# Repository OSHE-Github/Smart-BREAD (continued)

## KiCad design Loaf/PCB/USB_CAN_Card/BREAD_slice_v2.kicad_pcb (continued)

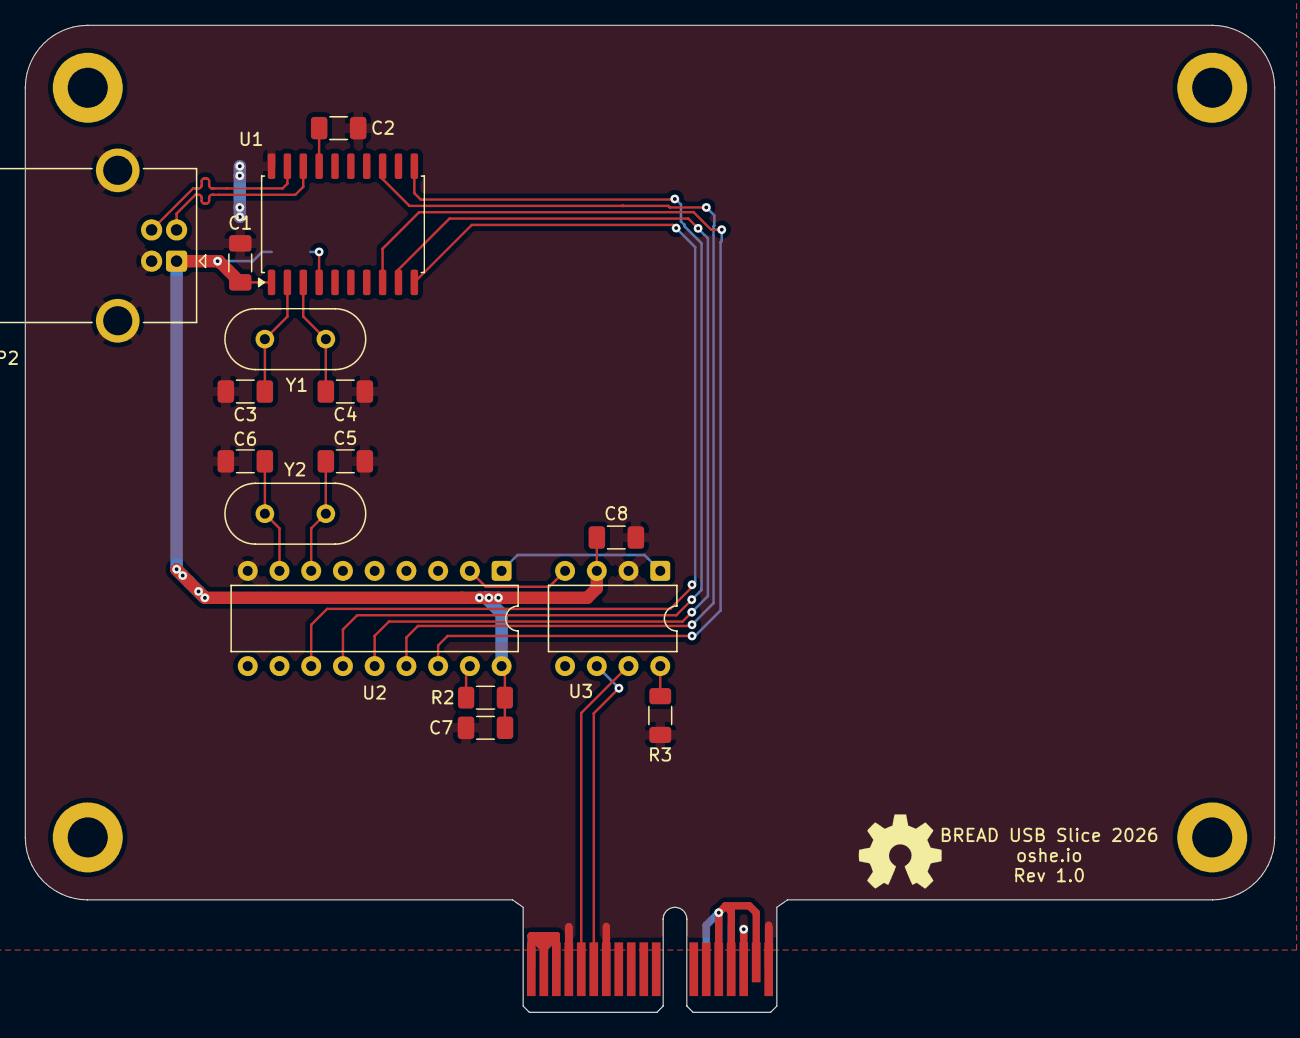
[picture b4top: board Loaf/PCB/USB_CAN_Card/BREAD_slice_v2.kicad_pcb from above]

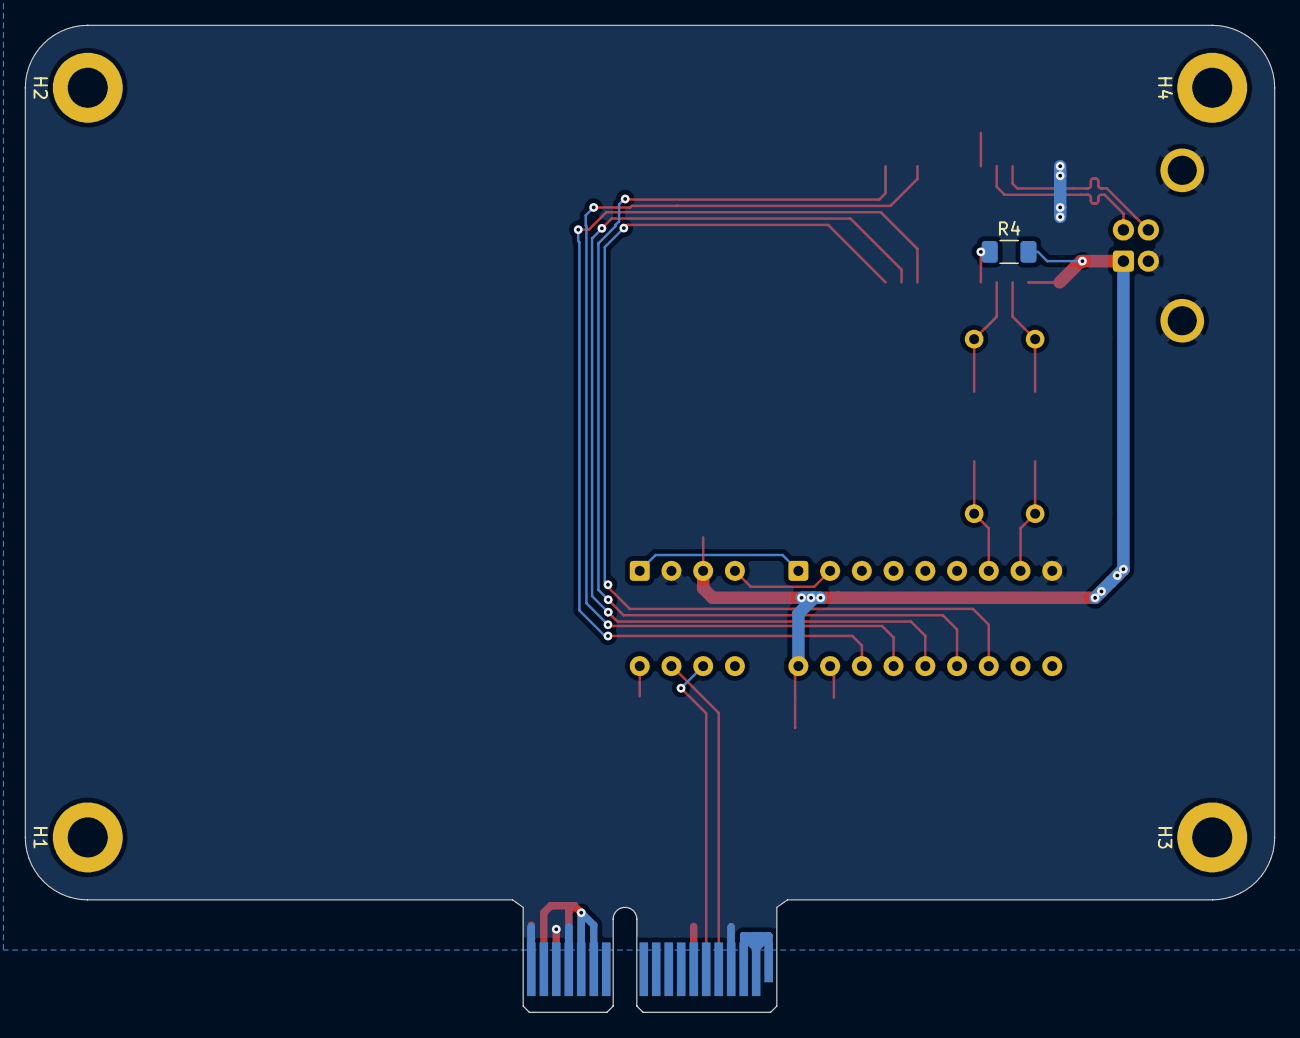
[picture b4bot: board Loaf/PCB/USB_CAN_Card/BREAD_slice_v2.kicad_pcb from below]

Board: 2 copper layers, 100.0 x 79.0 mm, 23 parts (5 on the bottom side), 24 nets.

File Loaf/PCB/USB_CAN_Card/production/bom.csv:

Designator,Footprint,Quantity,Value,LCSC Part #
C1,1206,1,1uF,
C2,1206,1,0.22-0.47uF,
"C3, C4, C5, C6",1206,4,20pf,
"C7, C8",1206,2,0.1uF,
J1,BUS_PCIexpress_x1,1,10018783-10200TLF,
LOGO1,OSHW-Symbol_6.7x6mm_SilkScreen,1,Logo_Open_Hardware_Small,
P2,USB_B_OST_USB-B1HSxx_Horizontal,1,USB_B,
"R2, R3, R4",1206,3,10k,
U1,SOIC-20W_7.5x12.8mm_P1.27mm,1,MCP2210x-SO,
U2,DIP-18_W7.62mm,1,MCP2515-xSO,
U3,DIP-8_W7.62mm,1,MCP2561-E-P,
Y1,Crystal_HC49-4H_Vertical,1,12MHZ Crystal,
Y2,Crystal_HC49-4H_Vertical,1,16MHZ Crystal,

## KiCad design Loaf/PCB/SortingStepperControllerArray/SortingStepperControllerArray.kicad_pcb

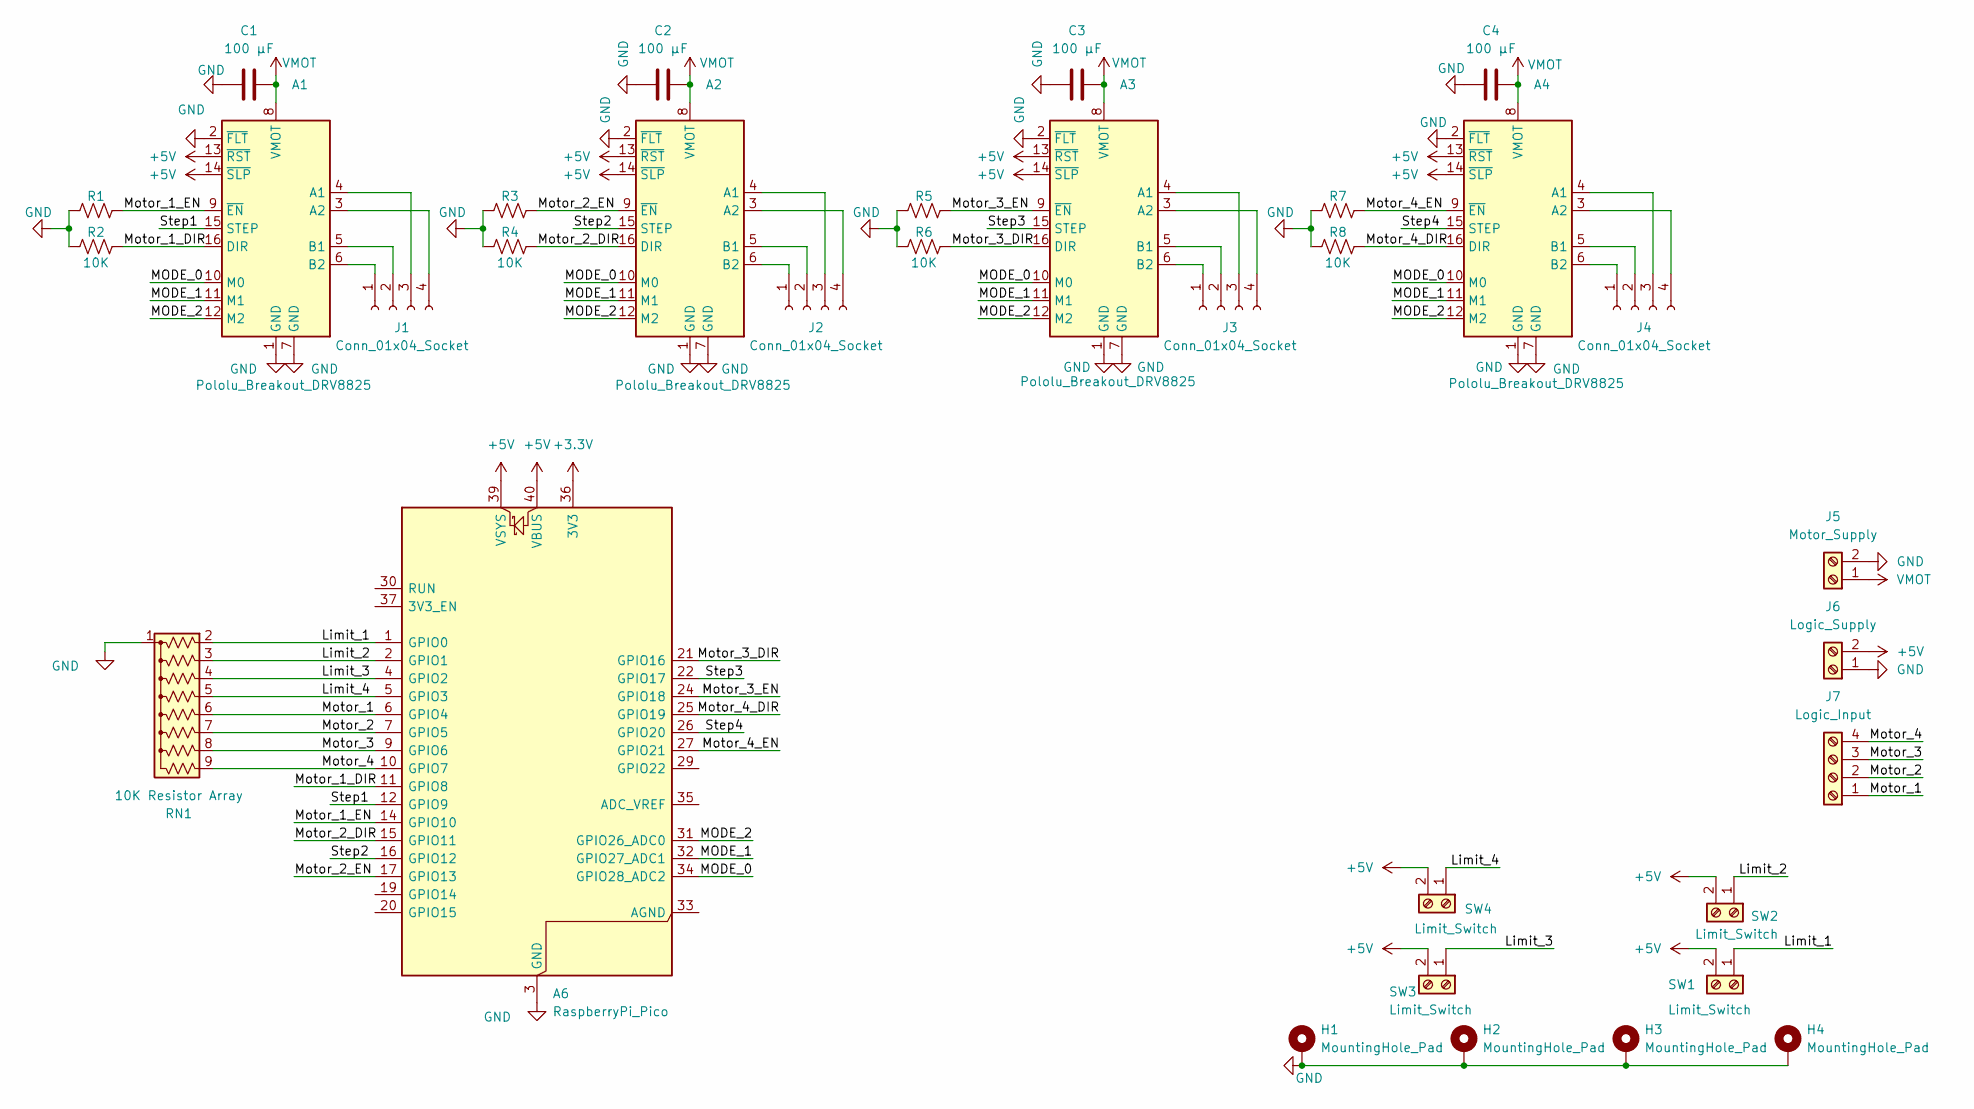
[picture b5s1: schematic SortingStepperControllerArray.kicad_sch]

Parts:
A1, A2, A3, A4: Pololu_Breakout_DRV8825; Pololu_Breakout-16_15.2x20.3mm
A6: RaspberryPi_Pico; RaspberryPi_Pico_Common_Unspecified
C1, C2, C3, C4: 100 µF; CP_Radial_D8.0mm_P3.50mm
H1, H2, H3, H4: MountingHole_Pad; MountingHole_3.2mm_M3_DIN965_Pad
J1, J2, J3, J4: Conn_01x04_Socket; JST_XH_B4B-XH-A_1x04_P2.50mm_Vertical
J5: Motor_Supply; TerminalBlock_TE_282834-2_1x02_P2.54mm_Horizontal
J6: Logic_Supply; TerminalBlock_TE_282834-2_1x02_P2.54mm_Horizontal
J7: Logic_Input; TerminalBlock_TE_282834-4_1x04_P2.54mm_Horizontal
R1, R2, R3, R4, R5, R6, R7, R8: 10K; R_1206_3216Metric_Pad1.30x1.75mm_HandSolder
RN1: 10K Resistor Array; R_Array_SIP9
SW1, SW2, SW3, SW4: Limit_Switch; TerminalBlock_TE_282834-2_1x02_P2.54mm_Horizontal

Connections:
+3.3V: A6.36 (3V3)
+5V: A1.13 (~RST), A1.14 (~SLP), A2.13 (~RST), A2.14 (~SLP), A3.13 (~RST), A3.14 (~SLP), A4.13 (~RST), A4.14 (~SLP), A6.39 (VSYS), A6.40 (VBUS), J6.2, SW1.2, SW2.2, SW3.2, SW4.2
/Limit_1: A6.1 (GPIO0), RN1.2 (R1), SW1.1
/Limit_2: A6.2 (GPIO1), RN1.3 (R2), SW2.1
/Limit_3: A6.4 (GPIO2), RN1.4 (R3), SW3.1
/Limit_4: A6.5 (GPIO3), RN1.5 (R4), SW4.1
/MODE_0: A1.10 (M0), A2.10 (M0), A3.10 (M0), A4.10 (M0), A6.34 (GPIO28_ADC2)
/MODE_1: A1.11 (M1), A2.11 (M1), A3.11 (M1), A4.11 (M1), A6.32 (GPIO27_ADC1)
/MODE_2: A1.12 (M2), A2.12 (M2), A3.12 (M2), A4.12 (M2), A6.31 (GPIO26_ADC0)
/Motor_1: A6.6 (GPIO4), J7.1, RN1.6 (R5)
/Motor_1_DIR: A1.16 (DIR), A6.11 (GPIO8), R2.2
/Motor_1_EN: A1.9 (~EN), A6.14 (GPIO10), R1.2
/Motor_2: A6.7 (GPIO5), J7.2, RN1.7 (R6)
/Motor_2_DIR: A2.16 (DIR), A6.15 (GPIO11), R4.2
/Motor_2_EN: A2.9 (~EN), A6.17 (GPIO13), R3.2
/Motor_3: A6.9 (GPIO6), J7.3, RN1.8 (R7)
/Motor_3_DIR: A3.16 (DIR), A6.21 (GPIO16), R6.2
/Motor_3_EN: A3.9 (~EN), A6.24 (GPIO18), R5.2
/Motor_4: A6.10 (GPIO7), J7.4, RN1.9 (R8)
/Motor_4_DIR: A4.16 (DIR), A6.25 (GPIO19), R8.2
/Motor_4_EN: A4.9 (~EN), A6.27 (GPIO21), R7.2
/Step1: A1.15 (STEP), A6.12 (GPIO9)
/Step2: A2.15 (STEP), A6.16 (GPIO12)
/Step3: A3.15 (STEP), A6.22 (GPIO17)
/Step4: A4.15 (STEP), A6.26 (GPIO20)
GND: A1.1 (GND), A1.2 (~FLT), A1.7 (GND), A2.1 (GND), A2.2 (~FLT), A2.7 (GND), A3.1 (GND), A3.2 (~FLT), A3.7 (GND), A4.1 (GND), A4.2 (~FLT), A4.7 (GND), A6.3 (GND), A6.8 (GND), A6.13 (GND), A6.18 (GND), A6.23 (GND), A6.28 (GND), A6.38 (GND), C1.1, C2.1, C3.1, C4.1, H1.1 (1_1), H2.1 (1_1), H3.1 (1_1), H4.1 (1_1), J5.2, J6.1, R1.1, R2.1, R3.1, R4.1, R5.1, R6.1, R7.1, R8.1, RN1.1 (common)
unnamed: A1.4 (A1), J1.3
unnamed: A1.3 (A2), J1.4
unnamed: A1.5 (B1), J1.2
unnamed: A1.6 (B2), J1.1
unnamed: A2.4 (A1), J2.3
unnamed: A2.3 (A2), J2.4
unnamed: A2.5 (B1), J2.2
unnamed: A2.6 (B2), J2.1
unnamed: A3.4 (A1), J3.3
unnamed: A3.3 (A2), J3.4
unnamed: A3.5 (B1), J3.2
unnamed: A3.6 (B2), J3.1
unnamed: A4.4 (A1), J4.3
unnamed: A4.3 (A2), J4.4
unnamed: A4.5 (B1), J4.2
unnamed: A4.6 (B2), J4.1
VMOT: A1.8 (VMOT), A2.8 (VMOT), A3.8 (VMOT), A4.8 (VMOT), C1.2, C2.2, C3.2, C4.2, J5.1

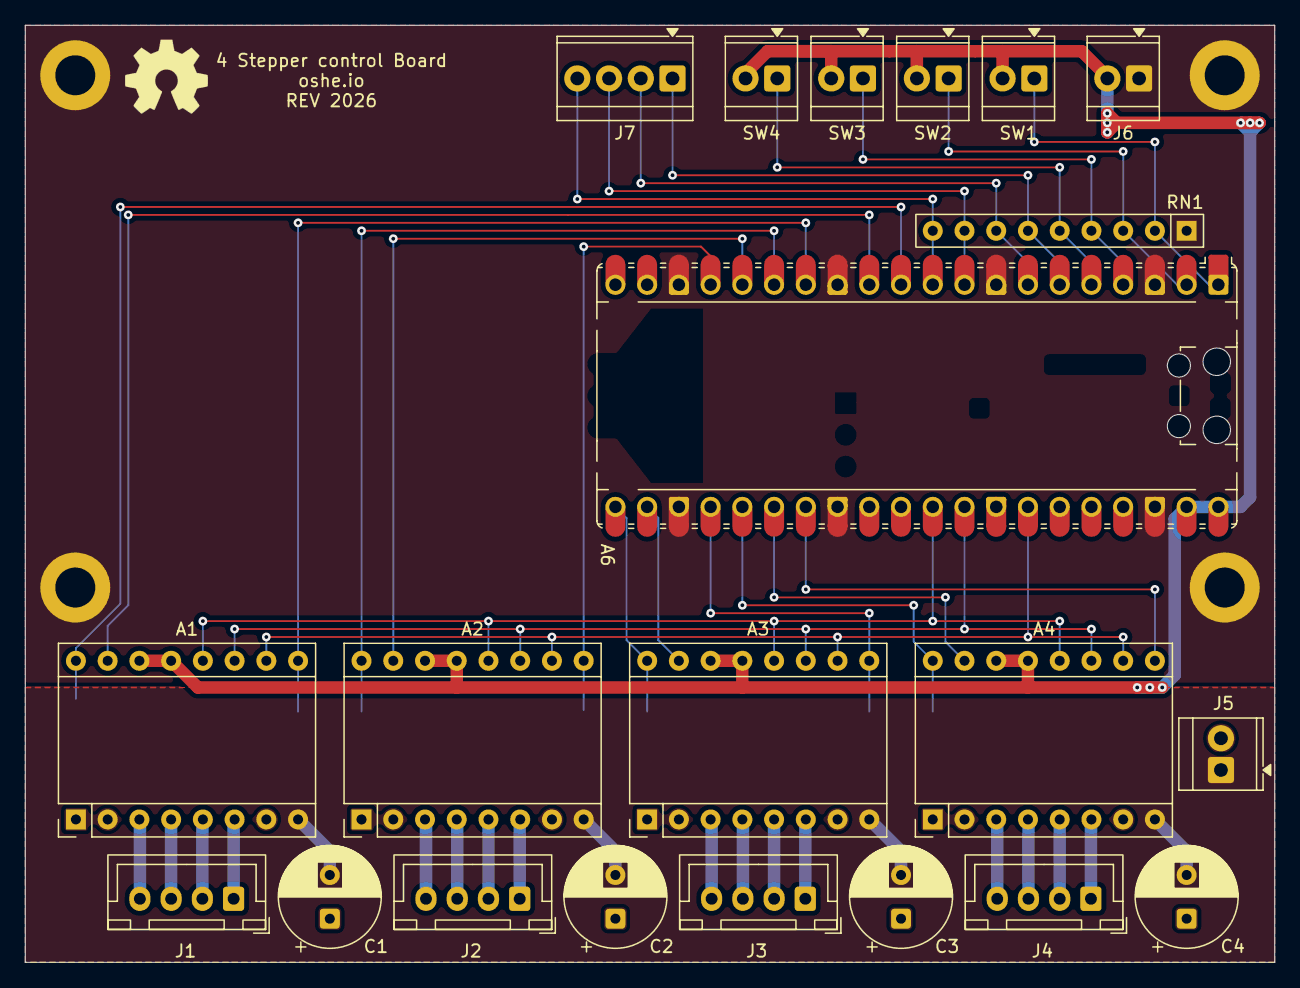
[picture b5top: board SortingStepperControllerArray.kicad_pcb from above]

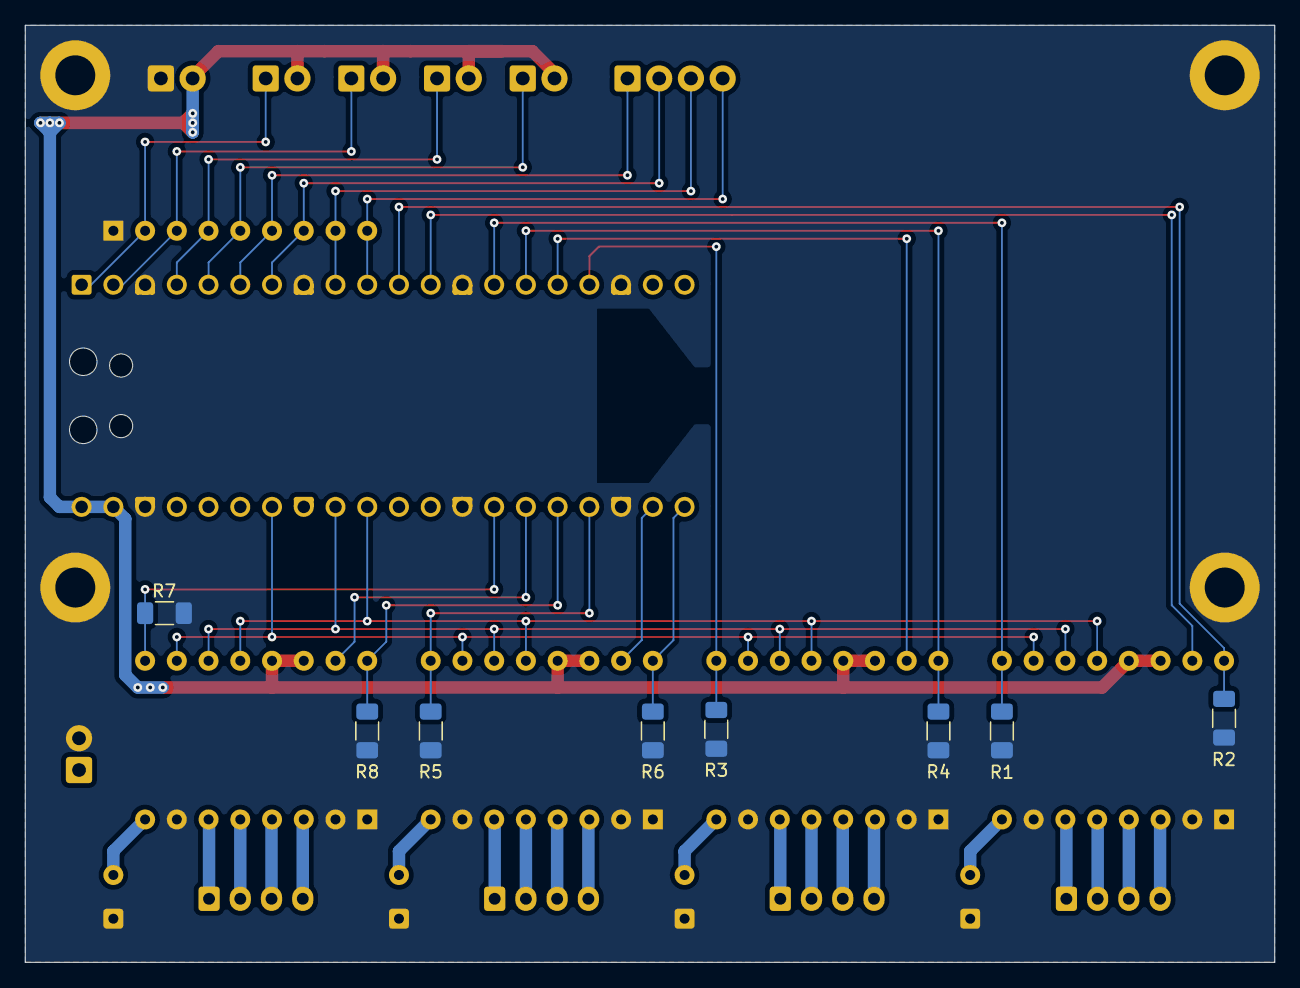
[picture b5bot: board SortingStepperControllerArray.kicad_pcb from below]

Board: 2 copper layers, 100.0 x 75.0 mm, 34 parts (8 on the bottom side), 42 nets.

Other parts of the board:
Logo1: Logo_Open_Hardware_Small; OSHW-Symbol_6.7x6mm_SilkScreen

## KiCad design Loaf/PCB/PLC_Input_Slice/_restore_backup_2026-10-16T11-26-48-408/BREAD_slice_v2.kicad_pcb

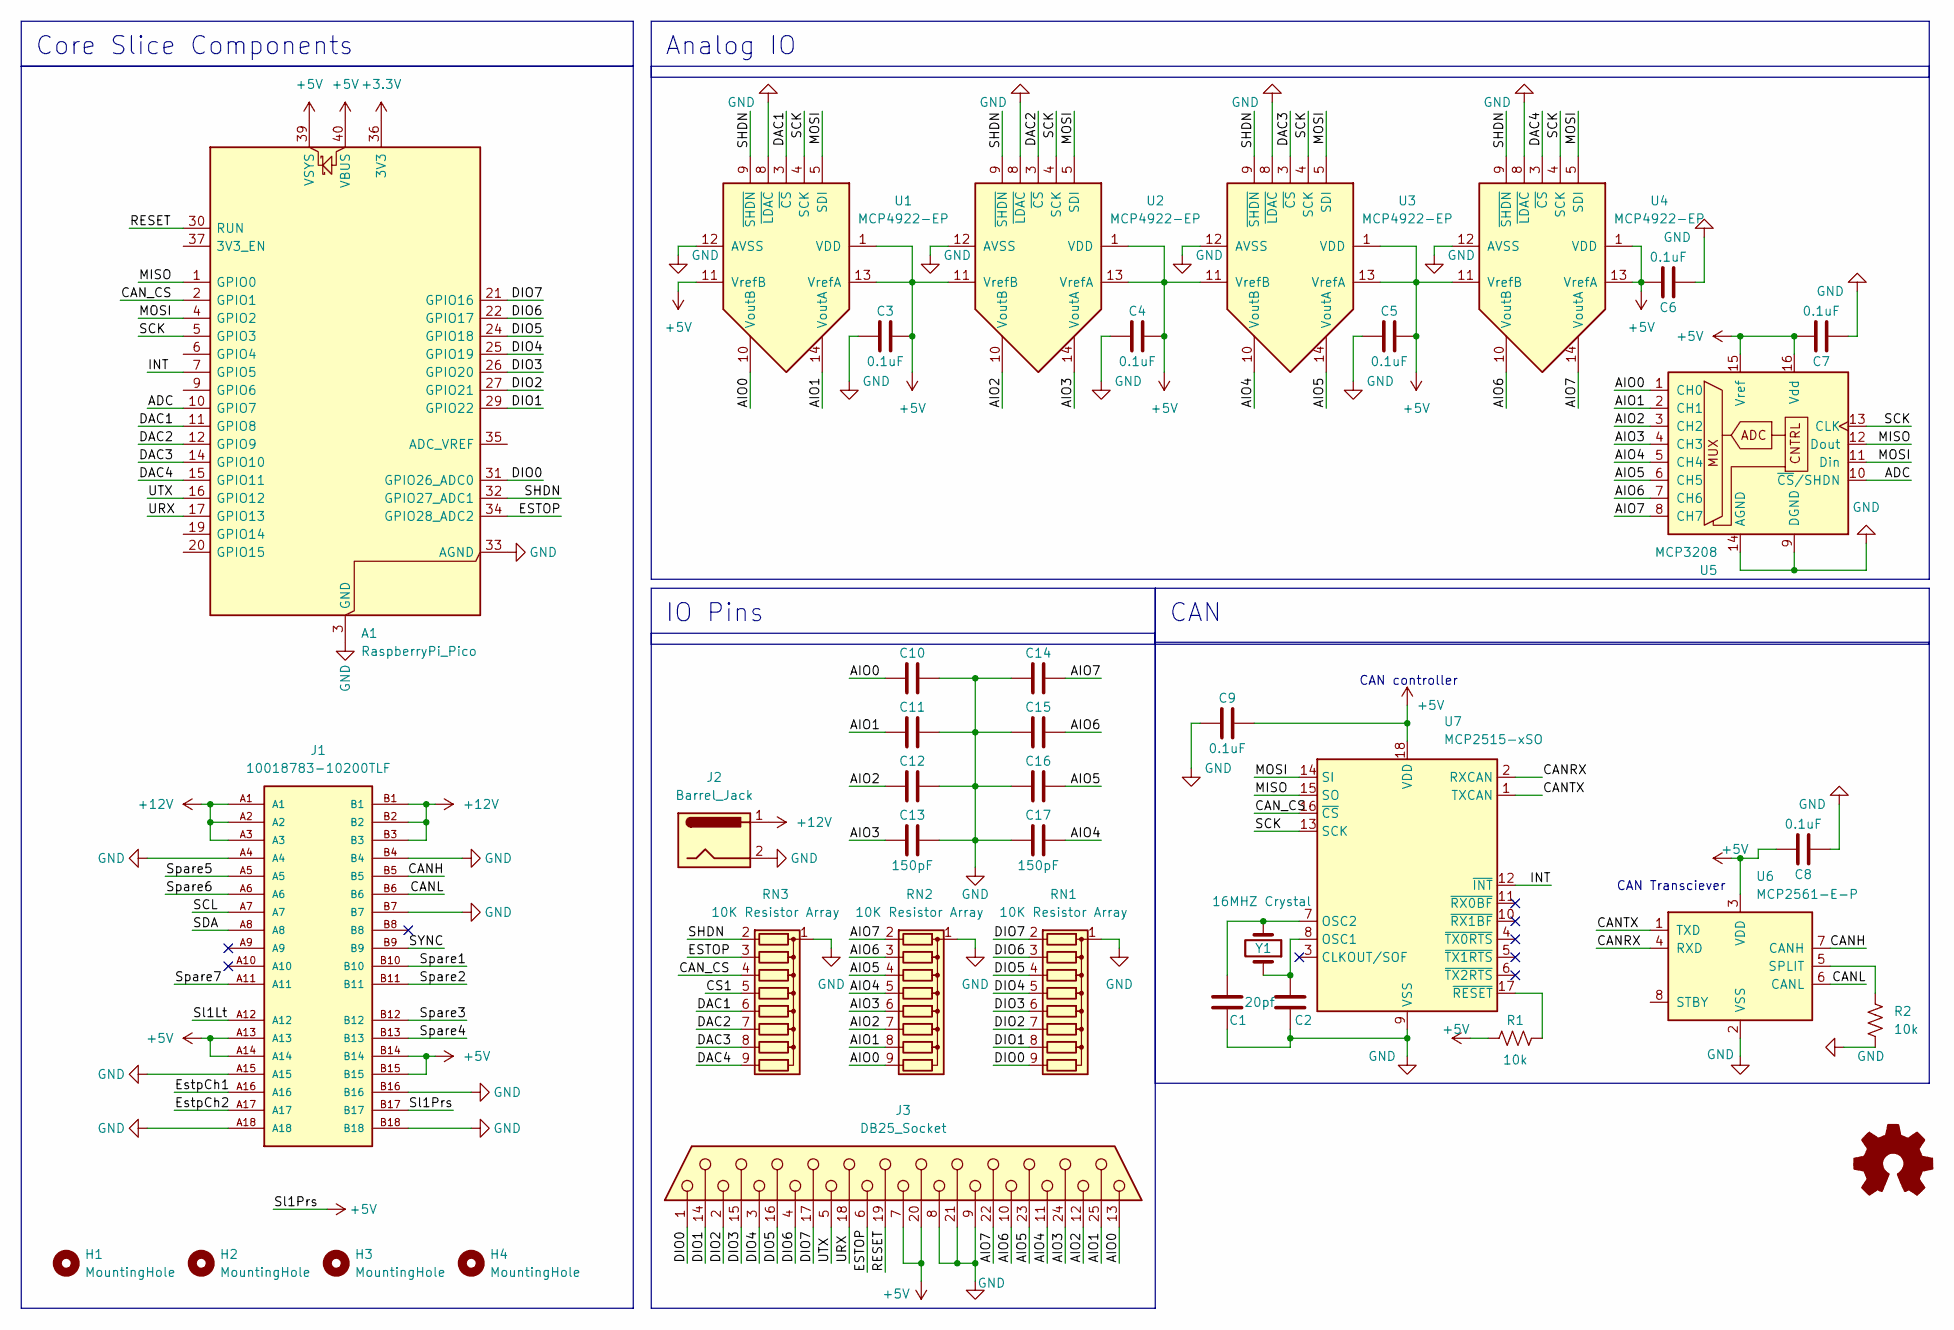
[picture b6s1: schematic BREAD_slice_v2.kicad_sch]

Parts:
A1: RaspberryPi_Pico; RaspberryPi_Pico_Common_Unspecified
C1, C2: 20pf; C_1206_3216Metric_Pad1.33x1.80mm_HandSolder
C3, C4, C5, C6, C7, C8, C9: 0.1uF; C_1206_3216Metric_Pad1.33x1.80mm_HandSolder
C10, C11, C12, C14, C15, C16: 10pF; C_1206_3216Metric_Pad1.33x1.80mm_HandSolder
C13, C17: 150pF; C_1206_3216Metric_Pad1.33x1.80mm_HandSolder
H1, H2, H3, H4: MountingHole; MountingHole_3.2mm_M3_DIN965_Pad
J1: 10018783-10200TLF; BUS_PCIexpress_x1; PARTREV Z
J2: Barrel_Jack; BarrelJack_CUI_PJ-063AH_Horizontal
J3: DB25_Socket; DSUB-25_Socket_Horizontal_P2.77x2.84mm_EdgePinOffset4.94mm_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
Logo1: Logo_Open_Hardware_Small; OSHW-Symbol_6.7x6mm_SilkScreen
R1, R2: 10k; R_1206_3216Metric_Pad1.30x1.75mm_HandSolder
RN1, RN2, RN3: 10K Resistor Array; R_Array_SIP9
U1, U2, U3, U4: MCP4922-EP; DIP-14_W7.62mm
U5: MCP3208; DIP-16_W7.62mm_LongPads
U6: MCP2561-E-P; DIP-8_W7.62mm
U7: MCP2515-xSO; DIP-18_W7.62mm
Y1: 16MHZ Crystal; Crystal_HC49-4H_Vertical

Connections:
+3.3V: A1.36 (3V3)
+5V: A1.39 (VSYS), A1.40 (VBUS), C3.2, C4.2, C5.2, C6.2, C7.2, C8.2, C9.2, J1.A13, J1.A14, J1.B14, J1.B15, J1.B17, J3.7, J3.20, R1.2, U1.1 (VDD), U1.11 (VrefB), U1.13 (VrefA), U2.1 (VDD), U2.11 (VrefB), U2.13 (VrefA), U3.1 (VDD), U3.11 (VrefB), U3.13 (VrefA), U4.1 (VDD), U4.11 (VrefB), U4.13 (VrefA), U5.15 (Vref), U5.16 (Vdd), U6.3 (VDD), U7.18 (VDD)
+12V: J1.A1, J1.A2, J1.A3, J1.B1, J1.B2, J1.B3, J2.1
/ADC: A1.10 (GPIO7), U5.10 (~CS/SHDN)
/AIO0: C10.1, J3.13, RN2.9 (R8), U1.10 (VoutB), U5.1 (CH0)
/AIO1: C11.1, J3.25, RN2.8 (R7), U1.14 (VoutA), U5.2 (CH1)
/AIO2: C12.1, J3.12, RN2.7 (R6), U2.10 (VoutB), U5.3 (CH2)
/AIO3: C13.1, J3.24, RN2.6 (R5), U2.14 (VoutA), U5.4 (CH3)
/AIO4: C17.2, J3.11, RN2.5 (R4), U3.10 (VoutB), U5.5 (CH4)
/AIO5: C16.2, J3.23, RN2.4 (R3), U3.14 (VoutA), U5.6 (CH5)
/AIO6: C15.2, J3.10, RN2.3 (R2), U4.10 (VoutB), U5.7 (CH6)
/AIO7: C14.2, J3.22, RN2.2 (R1), U4.14 (VoutA), U5.8 (CH7)
/CANH: J1.B5, U6.7 (CANH)
/CANL: J1.B6, U6.6 (CANL)
/CANRX: U6.4 (RXD), U7.2 (RXCAN)
/CANTX: U6.1 (TXD), U7.1 (TXCAN)
/CAN_CS: A1.2 (GPIO1), RN3.4 (R3), U7.16 (~CS)
/CS1: RN3.5 (R4)
/DAC1: A1.11 (GPIO8), RN3.6 (R5), U1.3 (~CS)
/DAC2: A1.12 (GPIO9), RN3.7 (R6), U2.3 (~CS)
/DAC3: A1.14 (GPIO10), RN3.8 (R7), U3.3 (~CS)
/DAC4: A1.15 (GPIO11), RN3.9 (R8), U4.3 (~CS)
/DIO0: A1.31 (GPIO26_ADC0), J3.1, RN1.9 (R8)
/DIO1: A1.29 (GPIO22), J3.14, RN1.8 (R7)
/DIO2: A1.27 (GPIO21), J3.2, RN1.7 (R6)
/DIO3: A1.26 (GPIO20), J3.15, RN1.6 (R5)
/DIO4: A1.25 (GPIO19), J3.3, RN1.5 (R4)
/DIO5: A1.24 (GPIO18), J3.16, RN1.4 (R3)
/DIO6: A1.22 (GPIO17), J3.4, RN1.3 (R2)
/DIO7: A1.21 (GPIO16), J3.17, RN1.2 (R1)
/ESTOP: A1.34 (GPIO28_ADC2), J3.6, RN3.3 (R2)
/EstpCh1: J1.A16
/EstpCh2: J1.A17
/INT: A1.7 (GPIO5), U7.12 (~INT)
/MISO: A1.1 (GPIO0), U5.12 (Dout), U7.15 (SO)
/MOSI: A1.4 (GPIO2), U1.5 (SDI), U2.5 (SDI), U3.5 (SDI), U4.5 (SDI), U5.11 (Din), U7.14 (SI)
/RESET: A1.30 (RUN), J3.19
/SCK: A1.5 (GPIO3), U1.4 (SCK), U2.4 (SCK), U3.4 (SCK), U4.4 (SCK), U5.13 (CLK), U7.13 (SCK)
/SCL: J1.A7
/SDA: J1.A8
/SHDN: A1.32 (GPIO27_ADC1), RN3.2 (R1), U1.9 (~SHDN), U2.9 (~SHDN), U3.9 (~SHDN), U4.9 (~SHDN)
/SYNC: J1.B9
/Sl1Lt: J1.A12
/Spare1: J1.B10
/Spare2: J1.B11
/Spare3: J1.B12
/Spare4: J1.B13
/Spare5: J1.A5
/Spare6: J1.A6
/Spare7: J1.A11
/URX: A1.17 (GPIO13), J3.18
/UTX: A1.16 (GPIO12), J3.5
GND: A1.3 (GND), A1.8 (GND), A1.13 (GND), A1.18 (GND), A1.23 (GND), A1.28 (GND), A1.33 (AGND), A1.38 (GND), C1.2, C2.2, C3.1, C4.1, C5.1, C6.1, C7.1, C8.1, C9.1, C10.2, C11.2, C12.2, C13.2, C14.1, C15.1, C16.1, C17.1, J1.A4, J1.A15, J1.A18, J1.B4, J1.B7, J1.B16, J1.B18, J2.2, J3.8, J3.9, J3.21, R2.1, RN1.1 (common), RN2.1 (common), RN3.1 (common), U1.8 (~LDAC), U1.12 (AVSS), U2.8 (~LDAC), U2.12 (AVSS), U3.8 (~LDAC), U3.12 (AVSS), U4.8 (~LDAC), U4.12 (AVSS), U5.9 (DGND), U5.14 (AGND), U6.2 (VSS), U7.9 (VSS)
unnamed: R2.2, U6.5 (SPLIT)
unnamed: C2.1, U7.8 (OSC1), Y1.1
unnamed: C1.1, U7.7 (OSC2), Y1.2
unnamed: R1.1, U7.17 (~RESET)

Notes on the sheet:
CAN Transciever
CAN controller
CAN
IO Pins
Analog IO
Core Slice Components

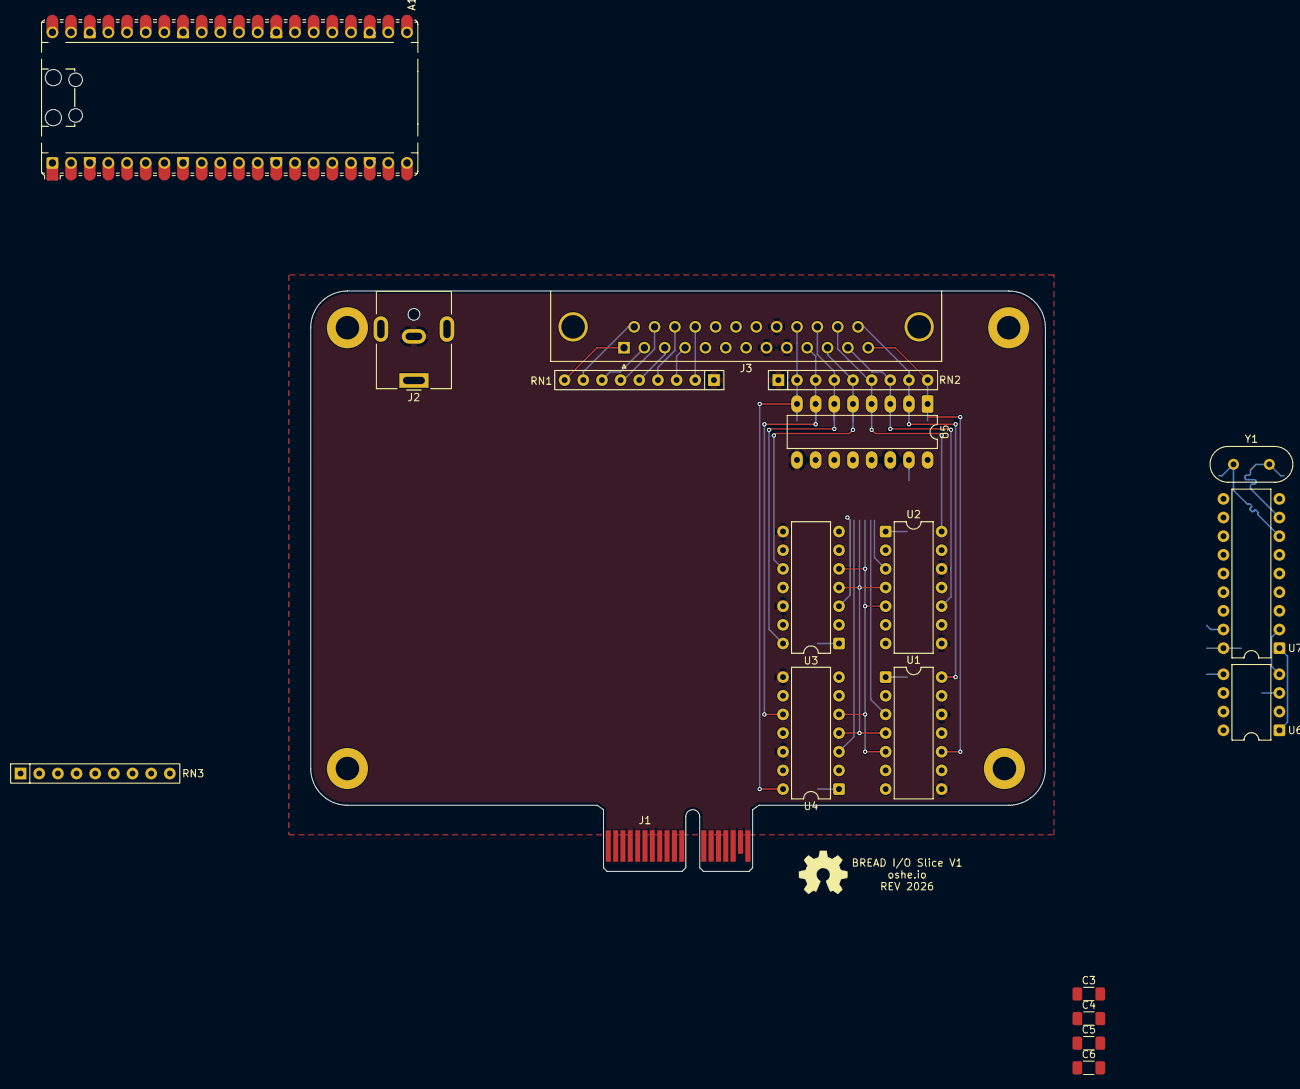
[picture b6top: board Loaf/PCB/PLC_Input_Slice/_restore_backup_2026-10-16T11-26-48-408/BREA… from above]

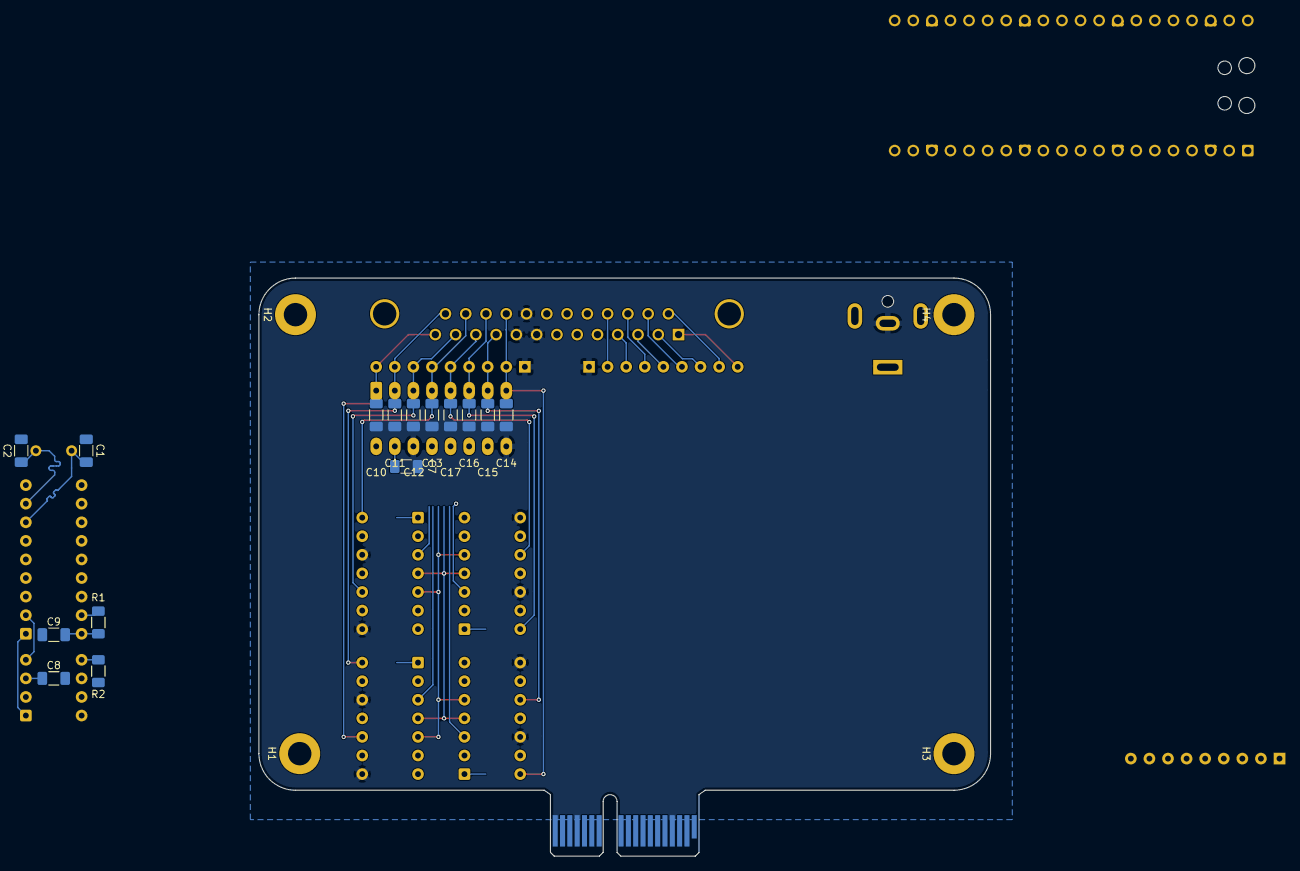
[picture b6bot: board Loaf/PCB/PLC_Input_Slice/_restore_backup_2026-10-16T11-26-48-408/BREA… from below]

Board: 2 copper layers, 100.0 x 79.0 mm, 39 parts (19 on the bottom side), 42 nets.

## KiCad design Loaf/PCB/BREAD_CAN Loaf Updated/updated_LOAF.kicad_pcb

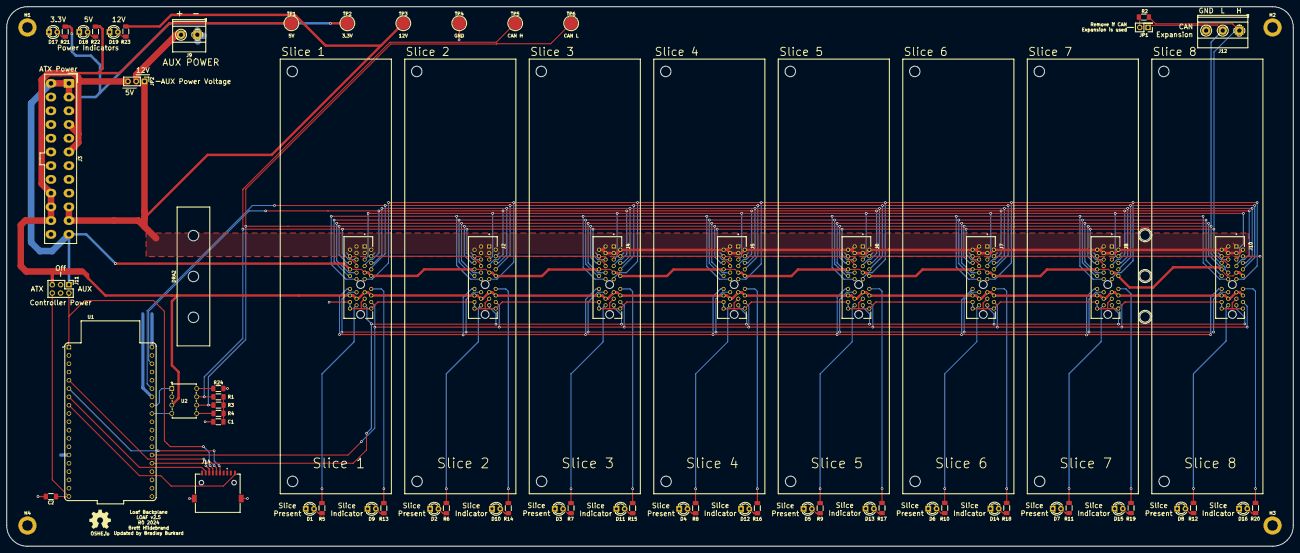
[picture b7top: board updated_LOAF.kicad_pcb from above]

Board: 2 copper layers, 393.7 x 165.1 mm, 91 parts (1 on the bottom side), 66 nets.

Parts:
C1: 4700pF; C_1206_3216Metric_Pad1.33x1.80mm_HandSolder
C2: 10uF_t; C_1206_3216Metric_Pad1.33x1.80mm_HandSolder
D1, D2, D3, D4, D5, D6, D7, D8, D9, D10, D11, D12, D13, D14, D15, D16, D17, D18, D19: LED; LED_D3.0mm
DRA1, DRA2: DIN_Rail_Adapter; DINRailAdapter_3xM3_PhoenixContact_1201578
H1, H2, H3, H4: MountingHole; MountingHole_3.2mm_M3_DIN965_Pad
H5, H6, H7, H8, H9, H10, H11, H12, H13, H14, H15, H16, H17, H18, H19, H20: MountingHole; MountingHole_3.2mm_M3
J1, J2, J4, J5, J6, J7, J8, J10: 10018783-10200TLF; AMPHENOL_10018783-10200TLF
J3: ATX-24; Molex_Mini-Fit_Jr_5566-24A_2x12_P4.20mm_Vertical
J9: Screw_Terminal_01x02; TerminalBlock_Phoenix_MKDS-1,5-2_1x02_P5.00mm_Horizontal
J11: Conn_02x03_Odd_Even; PinHeader_2x03_P2.54mm_Vertical
J12: Screw_Terminal_01x03; TerminalBlock_Phoenix_MKDS-1,5-3-5.08_1x03_P5.08mm_Horizont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
J14: MSD-11-A; CUI_MSD-11-A
JP1: Jumper_2_Bridged; PinHeader_2x01_P2.54mm_Vertical
JP2: Jumper_3_Bridged12; PinHeader_1x03_P2.54mm_Vertical
Logo1: Logo_Open_Hardware_Small; OSHW-Symbol_6.7x6mm_SilkScreen
R1, R3: 60; R_1206_3216Metric_Pad1.30x1.75mm_HandSolder
R2: 120; R_1206_3216Metric_Pad1.30x1.75mm_HandSolder
R4: 300; R_1206_3216Metric_Pad1.30x1.75mm_HandSolder
R5, R6, R7, R8, R9, R10, R11, R12, R13, R14, R15, R16, R17, R18, R19, R20, R21, R22, R23: R_US; R_1206_3216Metric_Pad1.30x1.75mm_HandSolder
R24: 10k; R_1206_3216Metric_Pad1.30x1.75mm_HandSolder
TP1, TP2, TP3, TP4, TP5, TP6: TestPoint; TestPoint_Pad_D4.0mm
U1: ESP32-DEVKITC-32E; MODULE_ESP32-DEVKITC-32E
U2: MCP2561FD-E/P; PDIP8_300MC_MCH

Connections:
+3.3V: J1.A9, J1.A10, J1.B8, J2.A9, J2.A10, J2.B8, J3.1 (+3.3V), J3.2 (+3.3V), J3.12 (+3.3V), J3.13 (+3.3V), J4.A9, J4.A10, J4.B8, J5.A9, J5.A10, J5.B8, J6.A9, J6.A10, J6.B8, J7.A9, J7.A10, J7.B8, J8.A9, J8.A10, J8.B8, J10.A9, J10.A10, J10.B8, J11.1, R21.1, TP2.1
+5V: J1.A13, J1.A14, J1.B14, J1.B15, J2.A13, J2.A14, J2.B14, J2.B15, J3.4 (+5V), J3.6 (+5V), J3.21 (+5V), J3.22 (+5V), J3.23 (+5V), J4.A13, J4.A14, J4.B14, J4.B15, J5.A13, J5.A14, J5.B14, J5.B15, J6.A13, J6.A14, J6.B14, J6.B15, J7.A13, J7.A14, J7.B14, J7.B15, J8.A13, J8.A14, J8.B14, J8.B15, J10.A13, J10.A14, J10.B14, J10.B15, J11.5, JP2.3 (B), R22.1, TP1.1, U2.3 (VDD)
+12V: J1.A1, J1.A2, J1.A3, J1.B1, J1.B2, J1.B3, J2.A1, J2.A2, J2.A3, J2.B1, J2.B2, J2.B3, J3.10 (+12V), J3.11 (+12V), J4.A1, J4.A2, J4.A3, J4.B1, J4.B2, J4.B3, J5.A1, J5.A2, J5.A3, J5.B1, J5.B2, J5.B3, J6.A1, J6.A2, J6.A3, J6.B1, J6.B2, J6.B3, J7.A1, J7.A2, J7.A3, J7.B1, J7.B2, J7.B3, J8.A1, J8.A2, J8.A3, J8.B1, J8.B2, J8.B3, J10.A1, J10.A2, J10.A3, J10.B1, J10.B2, J10.B3, JP2.1 (A), R23.1, TP3.1
/CANH: J1.B5, J2.B5, J4.B5, J5.B5, J6.B5, J7.B5, J8.B5, J10.B5, J12.1, R1.1, R2.1, TP5.1, U2.7 (CANH)
/CANL: J1.B6, J2.B6, J4.B6, J5.B6, J6.B6, J7.B6, J8.B6, J10.B6, J12.2, JP1.1 (A), R3.2, TP6.1, U2.6 (CANL)
/EstpCh1: J1.A16, J2.A16, J4.A16, J5.A16, J6.A16, J7.A16, J8.A16, J10.A16, U1.J3_14 (IO0)
/EstpCh2: J1.A17, J2.A17, J4.A17, J5.A17, J6.A17, J7.A17, J8.A17, J10.A17, U1.J3_15 (IO2)
/RX: U1.J3_9 (IO18), U2.4 (RXD)
/SCL: J1.A7, J2.A7, J4.A7, J5.A7, J6.A7, J7.A7, J8.A7, J10.A7, U1.J3_3 (IO22)
/SDA: J1.A8, J2.A8, J4.A8, J5.A8, J6.A8, J7.A8, J8.A8, J10.A8, U1.J3_6 (IO21)
/SPLIT: R4.1, U2.5 (SPLIT)
/STBY: R24.1, U2.8 (STBY)
/SYNC: J1.B9, J2.B9, J4.B9, J5.B9, J6.B9, J7.B9, J8.B9, J10.B9
/Spare1: J1.B10, J2.B10, J4.B10, J5.B10, J6.B10, J7.B10, J8.B10, J10.B10
/Spare2: J1.B11, J2.B11, J4.B11, J5.B11, J6.B11, J7.B11, J8.B11, J10.B11
/Spare3: J1.B12, J2.B12, J4.B12, J5.B12, J6.B12, J7.B12, J8.B12, J10.B12
/Spare4: J1.B13, J2.B13, J4.B13, J5.B13, J6.B13, J7.B13, J8.B13, J10.B13
/Spare5: J1.A5, J2.A5, J4.A5, J5.A5, J6.A5, J7.A5, J8.A5, J10.A5
/Spare6: J1.A6, J2.A6, J4.A6, J5.A6, J6.A6, J7.A6, J8.A6, J10.A6
/Spare7: J1.A11, J2.A11, J4.A11, J5.A11, J6.A11, J7.A11, J8.A11, J10.A11
/TX: U1.J3_8 (IO19), U2.1 (TXD)
CLK: J14.P5 (CLK), U1.J2_5 (IO34)
CS: J14.CD, U1.J2_8 (IO33)
ESP 3V3: J11.2, J14.P4 (VDD), U1.J2_1 (3V3)
ESP 5V: C2.1, J11.6, U1.J2_19 (EXT_5V)
GND: C1.2, C2.2, D1.1 (K), D2.1 (K), D3.1 (K), D4.1 (K), D5.1 (K), D6.1 (K), D7.1 (K), D8.1 (K), D9.1 (K), D10.1 (K), D11.1 (K), D12.1 (K), D13.1 (K), D14.1 (K), D15.1 (K), D16.1 (K), D17.1 (K), D18.1 (K), D19.1 (K), J1.A4, J1.A15, J1.A18, J1.B4, J1.B7, J1.B16, J1.B18, J2.A4, J2.A15, J2.A18, J2.B4, J2.B7, J2.B16, J2.B18, J3.3 (GND), J3.5 (GND), J3.7 (GND), J3.15 (GND), J3.17 (GND), J3.18 (GND), J3.19 (GND), J3.24 (GND), J4.A4, J4.A15, J4.A18, J4.B4, J4.B7, J4.B16, J4.B18, J5.A4, J5.A15, J5.A18, J5.B4, J5.B7, J5.B16, J5.B18, J6.A4, J6.A15, J6.A18, J6.B4, J6.B7, J6.B16, J6.B18, J7.A4, J7.A15, J7.A18, J7.B4, J7.B7, J7.B16, J7.B18, J8.A4, J8.A15, J8.A18, J8.B4, J8.B7, J8.B16, J8.B18, J9.1, J10.A4, J10.A15, J10.A18, J10.B4, J10.B7, J10.B16, J10.B18, J12.3, J14.G1 (COVER_GND), J14.G2 (COVER_GND__1), J14.P6 (VSS), R24.2, TP4.1, U1.J2_14 (GND_J2_14), U1.J3_1 (GND_J3_1), U1.J3_7 (GND_J3_7), U2.2 (VSS)
MISO: J14.P7 (DAT0), U1.J2_7 (IO32)
MOSI: J14.P3 (CMD), U1.J2_6 (IO35)
unnamed: C1.1, R1.2, R3.1, R4.2
unnamed: D1.2 (A), R5.2
unnamed: D2.2 (A), R6.2
unnamed: D3.2 (A), R7.2
unnamed: D4.2 (A), R8.2
unnamed: D5.2 (A), R9.2
unnamed: D6.2 (A), R10.2
unnamed: D7.2 (A), R11.2
unnamed: D8.2 (A), R12.2
unnamed: D9.2 (A), R13.2
unnamed: D10.2 (A), R14.2
unnamed: D11.2 (A), R15.2
unnamed: D12.2 (A), R16.2
unnamed: D13.2 (A), R17.2
unnamed: D14.2 (A), R18.2
unnamed: D15.2 (A), R19.2
unnamed: D16.2 (A), R20.2
unnamed: D17.2 (A), R21.2
unnamed: D18.2 (A), R22.2
unnamed: D19.2 (A), R23.2
unnamed: J9.2, JP2.2 (C)
unnamed: JP1.2 (B), R2.2
Sl1Lt: J1.A12, R13.1
Sl1Prs: J1.B17, R5.1
Sl2Lt: J2.A12, R14.1
Sl2Prs: J2.B17, R6.1
Sl3Lt: J4.A12, R15.1
Sl3Prs: J4.B17, R7.1
Sl4Lt: J5.A12, R16.1
Sl4Prs: J5.B17, R8.1
Sl5Lt: J6.A12, R17.1
Sl5Prs: J6.B17, R9.1
Sl6Lt: J7.A12, R18.1
Sl6Prs: J7.B17, R10.1
Sl7Lt: J8.A12, R19.1
Sl7Prs: J8.B17, R11.1
Sl8Lt: J10.A12, R20.1
Sl8Prs: J10.B17, R12.1
